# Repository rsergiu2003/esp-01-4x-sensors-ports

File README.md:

# PCB for esp-01, with 4 sensors headers
A simple pcb on which you can connect 4 sensors to the 4 gpio pins, also it has a voltage stabilizer which can take up to 30V (so you can safely power it up from 5,12,24V source)

The board has 4 pin headers (3 pins) with Signal, 3.3v, GND, each signal is connected to a GPIO pin (0,1,2,3) of the esp-01, so they can be used for reading sensors values.

## Features
  - each pin has a pull up resistor
  - 3.3 Voltage stabilizer
  - capacitor for voltage fluctuations
  - power indicator LED
  
## Testing
The board was tested with DHT22, DHT11, DS18B20, but is should work with any digital sensor working on 3.3V.

## Software
Here are some repositories you can check out for using with this board.

## 3D Model
You can see the fusion360 model here : https://a360.co/2FeM3dN you can download it and test it in your own context if you have to, this is very usefull if you want to use it in a box, or just to see how it looks in real life.

## More info
If you want more info feel free to leave me a message !

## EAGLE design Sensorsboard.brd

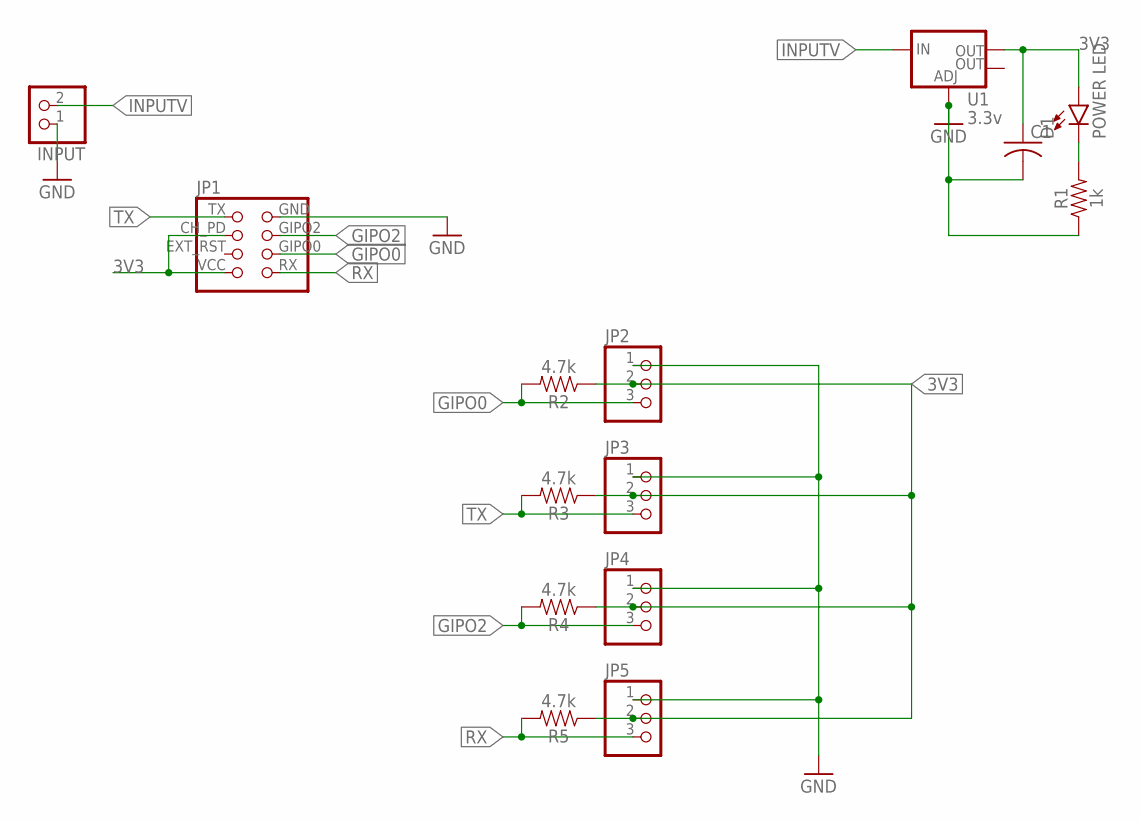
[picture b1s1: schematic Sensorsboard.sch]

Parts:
C1: C-USC1206K; C1206K
D1: POWER LED; LED-0805
INPUT: PINHD-1X2; 1X02
JP1: ESP-01-FEMALE
JP2, JP3, JP4, JP5: PINHD-1X3; 1X03
R1: 1k; 0805
R2, R3, R4, R5: 4.7k; 0805
U1: 3.3v; SOT223

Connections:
3V3: C1.1, D1.+ (A), JP1.CH_PD (CHIP_EN), JP1.VCC, JP2.2, JP3.2, JP4.2, JP5.2, R2.1, R3.1, R4.1, R5.1, U1.2 (OUT)
GIPO0: JP1.GIPO0, JP2.3, R2.2
GIPO2: JP1.GIPO2, JP4.3, R4.2
GND: C1.2, INPUT.1, JP1.GND, JP2.1, JP3.1, JP4.1, JP5.1, R1.1, U1.1 (ADJ)
INPUTV: INPUT.2, U1.3 (IN)
unnamed: D1.- (C), R1.2
RX: JP1.RX, JP5.3, R5.2
TX: JP1.TX, JP3.3, R3.2

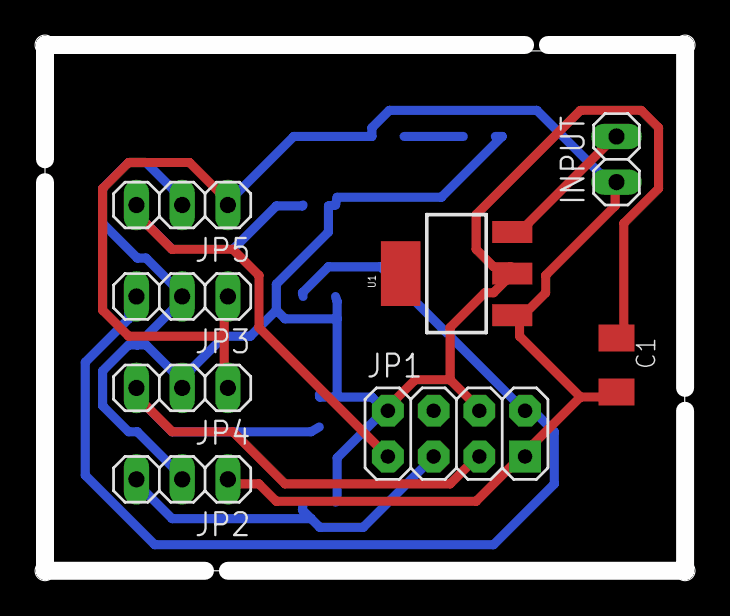
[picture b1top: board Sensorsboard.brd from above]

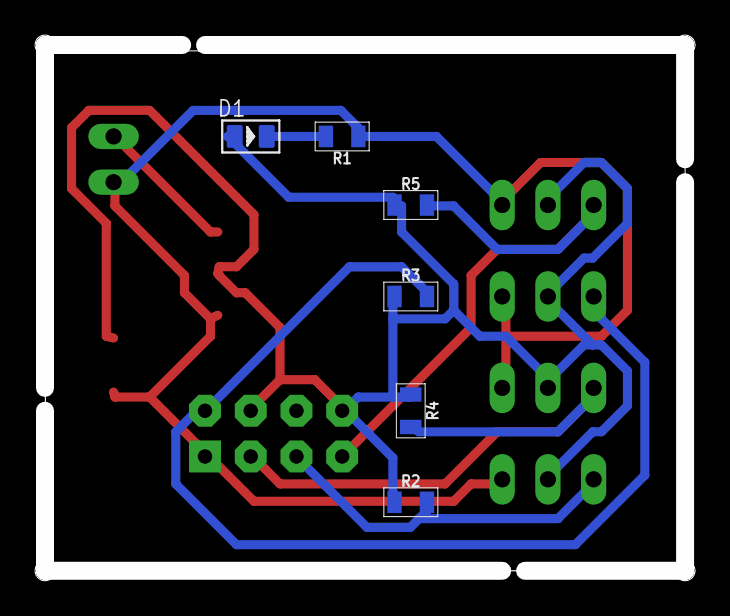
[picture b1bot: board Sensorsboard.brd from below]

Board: 2 copper layers, 35.6 x 29.2 mm, 14 parts (6 on the bottom side), 8 nets.

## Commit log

2019-01-06 initial import
2019-01-06 add imges for print
2019-01-06 cleanup
2019-01-06 sketch image
2019-01-06 add milling files for CNC
2019-01-06 git ignore
2019-05-01 stuff
